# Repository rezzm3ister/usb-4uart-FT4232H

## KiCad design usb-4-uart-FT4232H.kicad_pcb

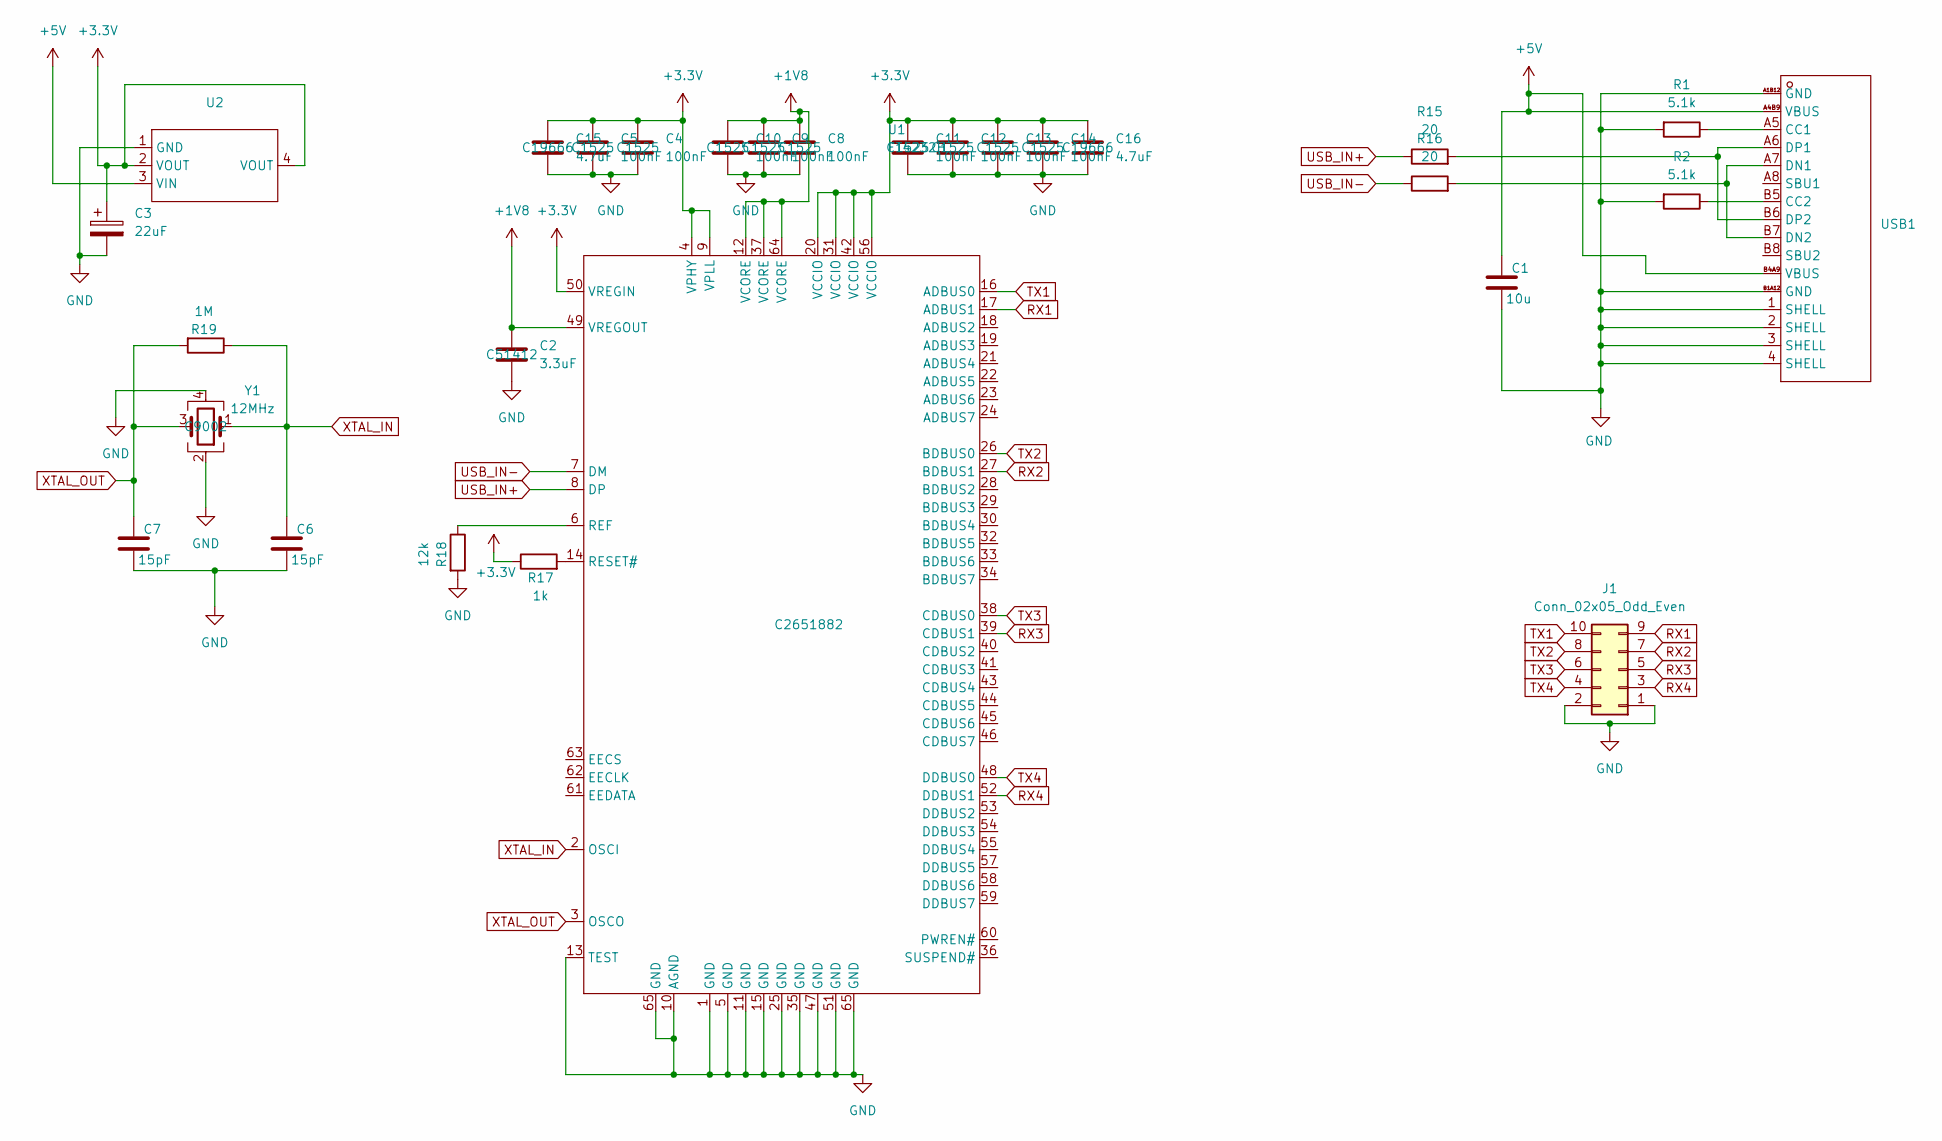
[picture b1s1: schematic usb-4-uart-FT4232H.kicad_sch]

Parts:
C1: 10u; C_0603_1608Metric; LCSC C19702
C2: 3.3uF; C_0603_1608Metric; LCSC C51412
C3: 22uF; CP_EIA-3216-18_Kemet-A; LCSC C7182
C4, C5, C8, C9, C10, C11, C12, C13, C14: 100nF; C_0402_1005Metric; LCSC C1525
C6, C7: 15pF; C_0402_1005Metric; LCSC C1548
C15, C16: 4.7uF; C_0603_1608Metric; LCSC C19666
J1: Conn_02x05_Odd_Even; PinHeader_2x05_P2.54mm_Horizontal; LCSC C60563
R1, R2: 5.1k; R_0402_1005Metric; LCSC C25905
R15, R16: 20; R_0603_1608Metric; LCSC C22950
R17: 1k; R_0402_1005Metric; LCSC C11702
R18: 12k; R_0402_1005Metric; LCSC C25752
R19: 1M; R_0402_1005Metric; LCSC C26083
U1: FT4232H; FT4242HQ-QFN-64_L9.0-W9.0-P0.50-BL-EP4.8; Manufacturer Part FT4232HQ-REEL; LCSC Part Name FT4232H 四通道高速USB转多用途UART/MPSSE IC
U2: AMS1117; Manufacturer Part AMS1117-3.3; LCSC Part Name 输出3.3V 1A
USB1: USB-C-SMD_TYPE-C16PIN; Manufacturer Part TYPE-C16PIN; LCSC Part Name Type-C 母 卧贴
Y1: 12MHz; Crystal_SMD_3225-4Pin_3.2x2.5mm; LCSC C9002

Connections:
+1V8: C2.1, C8.1, C9.1, C10.1, U1.12 (VCORE), U1.37 (VCORE), U1.49 (VREGOUT), U1.64 (VCORE)
+3.3V: C3.1, C4.1, C5.1, C11.1, C12.1, C13.1, C14.1, C15.1, C16.1, R17.1, U1.4 (VPHY), U1.9 (VPLL), U1.20 (VCCIO), U1.31 (VCCIO), U1.42 (VCCIO), U1.50 (VREGIN), U1.56 (VCCIO), U2.2 (VOUT), U2.4 (VOUT)
+5V: C1.1, U2.3 (VIN), USB1.A4B9 (VBUS), USB1.B4A9 (VBUS)
GND: C1.2, C2.2, C3.2, C4.2, C5.2, C6.2, C7.2, C8.2, C9.2, C10.2, C11.2, C12.2, C13.2, C14.2, C15.2, C16.2, J1.1, J1.2, R1.2, R2.2, R18.2, U1.1 (GND), U1.5 (GND), U1.10 (AGND), U1.11 (GND), U1.13 (TEST), U1.15 (GND), U1.25 (GND), U1.35 (GND), U1.47 (GND), U1.51 (GND), U1.65 (GND), U2.1 (GND), USB1.1 (SHELL), USB1.2 (SHELL), USB1.3 (SHELL), USB1.4 (SHELL), USB1.A1B12 (GND), USB1.B1A12 (GND), Y1.2, Y1.4
unnamed: R18.1, U1.6 (REF)
unnamed: R17.2, U1.14 (RESET#)
unnamed: R1.1, USB1.A5 (CC1)
unnamed: R2.1, USB1.B5 (CC2)
unnamed: R16.2, USB1.A7 (DN1), USB1.B7 (DN2)
unnamed: R15.2, USB1.A6 (DP1), USB1.B6 (DP2)
RX1: J1.9, U1.17 (ADBUS1)
RX2: J1.7, U1.27 (BDBUS1)
RX3: J1.5, U1.39 (CDBUS1)
RX4: J1.3, U1.52 (DDBUS1)
TX1: J1.10, U1.16 (ADBUS0)
TX2: J1.8, U1.26 (BDBUS0)
TX3: J1.6, U1.38 (CDBUS0)
TX4: J1.4, U1.48 (DDBUS0)
USB_IN+: R15.1, U1.8 (DP)
USB_IN-: R16.1, U1.7 (DM)
XTAL_IN: C6.1, R19.1, U1.2 (OSCI), Y1.1
XTAL_OUT: C7.1, R19.2, U1.3 (OSCO), Y1.3

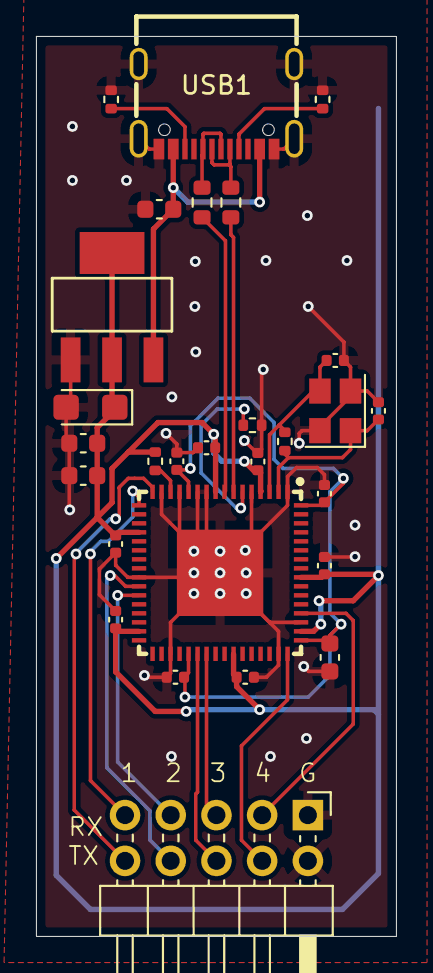
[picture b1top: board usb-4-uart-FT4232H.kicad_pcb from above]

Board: 2 copper layers, 20.0 x 50.0 mm, 28 parts (0 on the bottom side), 22 nets.

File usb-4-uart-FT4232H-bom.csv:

"Reference","Value","Footprint","Datasheet","Qty","LCSC","Supplier","Supplier Part","DNP","Exclude from BOM","Exclude from Board"
"C1","10u","Capacitor_SMD:C_0603_1608Metric","~","1","C19702 ","","","","",""
"C2","3.3uF","Capacitor_SMD:C_0603_1608Metric","~","1","C51412","","","","",""
"C3","22uF","Capacitor_Tantalum_SMD:CP_EIA-3216-18_Kemet-A","~","1","C7182","","","","",""
"C4,C5,C8,C9,C10,C11,C12,C13,C14","100nF","Capacitor_SMD:C_0402_1005Metric","~","9","C1525","","","","",""
"C6,C7","15pF","Capacitor_SMD:C_0402_1005Metric","~","2","C1548","","","","",""
"C15,C16","4.7uF","Capacitor_SMD:C_0603_1608Metric","~","2","C19666","","","","",""
"J1","Conn_02x05_Odd_Even","Connector_PinHeader_2.54mm:PinHeader_2x05_P2.54mm_Horizontal","~","1","C60563","","","","",""
"R1,R2","5.1k","Resistor_SMD:R_0402_1005Metric","~","2","C25905","","","","",""
"R15,R16","20","Resistor_SMD:R_0603_1608Metric","~","2","C22950","","","","",""
"R17","1k","Resistor_SMD:R_0402_1005Metric","~","1","C11702","","","","",""
"R18","12k","Resistor_SMD:R_0402_1005Metric","~","1","C25752","","","","",""
"R19","1M","Resistor_SMD:R_0402_1005Metric","~","1","C26083","","","","",""
"U1","FT4232H","JLCLibrary:FT4242HQ-QFN-64_L9.0-W9.0-P0.50-BL-EP4.8","https://atta.szlcsc.com/upload/public/pdf/source/20201230/C5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","1","C2651882","LCSC","C2651882","","",""
"U2","~","JLCLibrary:AMS1117","https://atta.szlcsc.com/upload/public/pdf/source/20180727/C6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","1","C6186","LCSC","C6186","","",""
"USB1","~","JLCLibrary:USB-C-SMD_TYPE-C16PIN","https://atta.szlcsc.com/upload/public/pdf/source/20190521/C3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","1","C393939","LCSC","C393939","","",""
"Y1","12MHz","Crystal:Crystal_SMD_3225-4Pin_3.2x2.5mm","~","1"," C9002","","","","",""

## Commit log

2025-05-10 added main version
2025-05-11 updated silkscreen
